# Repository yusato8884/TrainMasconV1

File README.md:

# TrainMasconV1

自作ゲーム「[Tozai Sim Pro](https://tozai-sim.base44.app/)」用の、USBキーボードとして動作する自作マスコン（主幹制御器）コントローラーです。
可変抵抗（2連ボリューム）のレバー位置を読み取り、ノッチ（P4〜N〜B7〜EB）に応じたキー入力をPCへ送ります。
現在のノッチは0.96インチOLEDに大きく表示されます。

- マイコン: AE-RP2040（MicroPython）
- 表示: SSD1306 OLED 128x64（I2C）
- 入力: 可変抵抗 1個（ADC）＋ ボタン 3個
- 接続: USB HID キーボード

ドキュメント: <https://y-trm1doc.base44.app/>

## ディレクトリ構成

```
Firmware/
  LICENSE                               ソフトウェアのライセンス（MIT）
  main.py                               本体ファームウェア（ノッチ→キー入力、OLED表示、USB HID）
  vrcalib.py                            可変抵抗の電圧測定ツール（ノッチ境界の電圧調整用）
Hardware/
  Enclosure/                            3Dプリント用ケース
    TRM1-Case-Top.stl                   ケース上部
    TRM1-Case-Bottom.stl                ケース下部
    TRM1-Case-Handle.stl                ハンドル
    TRM1-Case-Handle-Stopper.stl        ハンドルのストッパー
  PCB/                                  基板データ
    ProPrj_Mascon_2026-09-23.epro2      EasyEDA Pro の原本
    kicad_output/                       KiCad 8 変換版
      Mascon.kicad_pro                  KiCad プロジェクトファイル
      Mascon.kicad_sch                  回路図
      Mascon.kicad_pcb                  基板
      Mascon.kicad_sym                  シンボルライブラリ
      Mascon.kicad_footprints.pretty/   フットプリントライブラリ（.kicad_mod 8点）
      fp-lib-table                      フットプリントライブラリ設定
      sym-lib-table                     シンボルライブラリ設定
      CONVERSION_NOTES.md               変換時の注意事項
  LICENSE                               ハードウェアのライセンス（CERN-OHL-P v2）
README.md                               このファイル
```

## 配線

| 部品 | ピン |
|---|---|
| OLED SDA / SCL | GP20 / GP19（SoftI2C, アドレス 0x3C） |
| ボタン1 / 2 / 3 | GP23 / GP24 / GP25（GND側に接続） |
| 可変抵抗（中点） | GP26 (ADC0)、両端は 3V3 と GND |

## セットアップ

1. AE-RP2040 に MicroPython を書き込みます。
2. 必要なライブラリを導入します。
   ```
   mpremote mip install ssd1306
   mpremote mip install usb-device-keyboard
   ```
3. `Firmware/main.py` を `main.py` として本体に転送します。
4. USBで接続すると、キーボードとして認識されます。

## ノッチの調整

1. `Firmware/vrcalib.py` を実行し、レバーを各ノッチに合わせたときの電圧を読み取ります。
2. `main.py` の `LAYERS` の電圧しきい値（下限V, 上限V）を書き換えます。

既定のキー割り当ては次のとおりです（電圧の低い側から）。

| ノッチ | P4 | P3 | P2 | P1 | N | B1〜B6 | B7 | EB |
|---|---|---|---|---|---|---|---|---|
| キー | 1 | 2 | 3 | 4 | → | 5, 6, 7, 8, 9, 0 | - | Space |

ボタン1を押しながら起動すると安全モード（HID初期化とメインループを行わない）になり、ファイルを編集できます。

## ハードウェア

- `Hardware/PCB/ProPrj_Mascon_2026-09-23.epro2` が基板の原本です。
- `Hardware/PCB/kicad_output/` は KiCad 8 向けの変換結果です（開く場合は `Mascon.kicad_pro` を指定します）。KiCad での動作確認は未実施のため、開く際は [CONVERSION_NOTES.md](Hardware/PCB/kicad_output/CONVERSION_NOTES.md) を確認してください。
- ケースのSTL（`Hardware/Enclosure/` 内の `TRM1-Case-*.stl` 4点）についての注意:
  - サポート材は含まれていません。造形方向やプリンターに応じて、必要ならスライサー側で追加してください。
  - 薄肉部分やクリアランス（はめ合いの隙間）は十分に考慮されていません。
  - そのため、3Dプリントサービスに発注するか、自分で造形する場合は精度の非常に高いプリンター（光造形など）が必要です。一般的なFDMプリンターでは、そのままでは組み立てられない可能性があります。

## ライセンス

ライセンスは、対象ごとにそれぞれのフォルダ内の `LICENSE` に記載されています。

| 対象 | ライセンス | ファイル |
|---|---|---|
| ハードウェア（`Hardware/` 配下: 基板、回路図、ケース） | [CERN-OHL-P v2](Hardware/LICENSE) | `Hardware/LICENSE` |
| ソフトウェア（`Firmware/` 配下） | [MIT](Firmware/LICENSE) | `Firmware/LICENSE` |

SPDX: `CERN-OHL-P-2.0`（ハードウェア）/ `MIT`（ソフトウェア）

[SCANOSS](https://www.scanoss.com/) によるスキャンでは、全ファイルで既存OSSとの一致は検出されませんでした（2026-09-24時点）。

---

# TrainMasconV1

A custom mascon (master controller) controller for my original game "[Tozai Sim Pro](https://tozai-sim.base44.app/)", which operates as a USB keyboard.
It reads the lever position of a variable resistor (dual-gang potentiometer) and sends key inputs to the PC according to the notch (P4〜N〜B7〜EB).
The current notch is displayed prominently on a 0.96-inch OLED.

- Microcontroller: AE-RP2040 (MicroPython)
- Display: SSD1306 OLED 128x64 (I2C)
- Input: 1 variable resistor (ADC) + 3 buttons
- Connection: USB HID keyboard

Documentation: <https://y-trm1doc.base44.app/>

## Directory Structure

```
Firmware/
  LICENSE                               Software license (MIT)
  main.py                               Main firmware (notch→key input, OLED display, USB HID)
  vrcalib.py                            Variable resistor voltage measurement tool (for adjusting notch boundary voltages)
Hardware/
  Enclosure/                            3D-printable case
    TRM1-Case-Top.stl                   Case top
    TRM1-Case-Bottom.stl                Case bottom
    TRM1-Case-Handle.stl                Handle
    TRM1-Case-Handle-Stopper.stl        Handle stopper
  PCB/                                  PCB data
    ProPrj_Mascon_2026-09-23.epro2      EasyEDA Pro original
    kicad_output/                       KiCad 8 converted version
      Mascon.kicad_pro                  KiCad project file
      Mascon.kicad_sch                  Schematic
      Mascon.kicad_pcb                  PCB layout
      Mascon.kicad_sym                  Symbol library
      Mascon.kicad_footprints.pretty/   Footprint library (8 .kicad_mod files)
      fp-lib-table                      Footprint library table
      sym-lib-table                     Symbol library table
      CONVERSION_NOTES.md               Notes on the conversion
  LICENSE                               Hardware license (CERN-OHL-P v2)
README.md                               This file
```

## Wiring

| Component | Pin |
|---|---|
| OLED SDA / SCL | GP20 / GP19（SoftI2C, address 0x3C） |
| Button 1 / 2 / 3 | GP23 / GP24 / GP25（connected to GND） |
| Variable resistor (center tap) | GP26 (ADC0), both ends to 3V3 and GND |

## Setup

1. Flash MicroPython onto the AE-RP2040.
2. Install the required libraries.
   ```
   mpremote mip install ssd1306
   mpremote mip install usb-device-keyboard
   ```
3. Transfer `Firmware/main.py` to the device as `main.py`.
4. When connected via USB, it will be recognized as a keyboard.

## Notch Adjustment

1. Run `Firmware/vrcalib.py` and measure the voltage when the lever is set to each notch.
2. Rewrite the voltage thresholds (lower limit V, upper limit V) in `LAYERS` in `main.py`.

The default key assignments are as follows (from the lower-voltage side).

| Notch | P4 | P3 | P2 | P1 | N | B1〜B6 | B7 | EB |
|---|---|---|---|---|---|---|---|---|
| Key | 1 | 2 | 3 | 4 | → | 5, 6, 7, 8, 9, 0 | - | Space |

Starting while holding Button 1 enters safe mode (HID initialization and the main loop are not executed), allowing files to be edited.

## Hardware

- `Hardware/PCB/ProPrj_Mascon_2026-09-23.epro2` is the original PCB design file.
- `Hardware/PCB/kicad_output/` contains the conversion results for KiCad 8 (open `Mascon.kicad_pro` to load the project). Since operation in KiCad has not been verified, check [CONVERSION_NOTES.md](Hardware/PCB/kicad_output/CONVERSION_NOTES.md) when opening the files.
- Notes on the case STL files (the four `TRM1-Case-*.stl` files in `Hardware/Enclosure/`):
  - Support material is not included. Add it in the slicer as necessary depending on the print orientation and printer.
  - Thin sections and clearances (gaps for fitting) have not been sufficiently taken into consideration.
  - Therefore, if ordering from a 3D printing service, or printing it yourself, a very high-precision printer (such as a resin printer) is required. With a typical FDM printer, it may not be possible to assemble it as-is.

## License

The license for each part is provided in the `LICENSE` file inside the corresponding folder.

| Target | License | File |
|---|---|---|
| Hardware (PCB, schematics, and case under `Hardware/`) | [CERN-OHL-P v2](Hardware/LICENSE) | `Hardware/LICENSE` |
| Software (under `Firmware/`) | [MIT](Firmware/LICENSE) | `Firmware/LICENSE` |

SPDX: `CERN-OHL-P-2.0` (hardware) / `MIT` (software)

According to a scan by [SCANOSS](https://www.scanoss.com/), no matches with existing OSS were detected across all files (as of 2026-09-24).

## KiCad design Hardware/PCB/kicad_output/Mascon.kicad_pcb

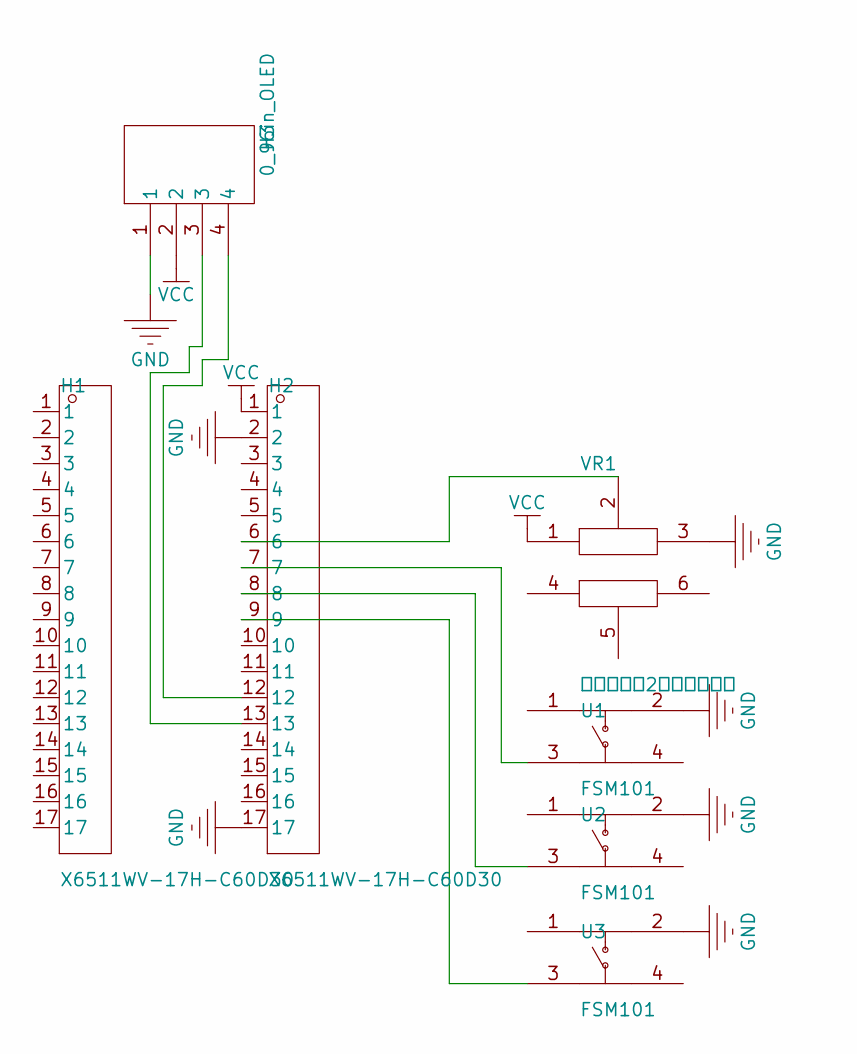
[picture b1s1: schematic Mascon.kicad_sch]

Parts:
H1, H2: X6511WV-17H-C60D30; HDR-TH_17P-P2.54-V-M; MPN X6511WV-17H-C60D30; LCSC C725949
H3: 0_96in_OLED
U1, U2, U3: FSM101; SW-TH_4P-L12.0-W12.0-P5.00-LS12.5; MPN FSM101; LCSC C5340381
VR1: 基板取付用2連ボリューム

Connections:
$1N9: H2.6, VR1.2
$1N14: H2.7, U1.3
$1N15: H2.8, U2.3
$1N16: H2.9, U3.3
$1N21: H2.12, H3.4
$1N22: H2.13, H3.3
GND: H2.2, H2.17, H3.1, U1.2, U2.2, U3.2, VR1.3
VCC: H2.1, H3.2, VR1.1

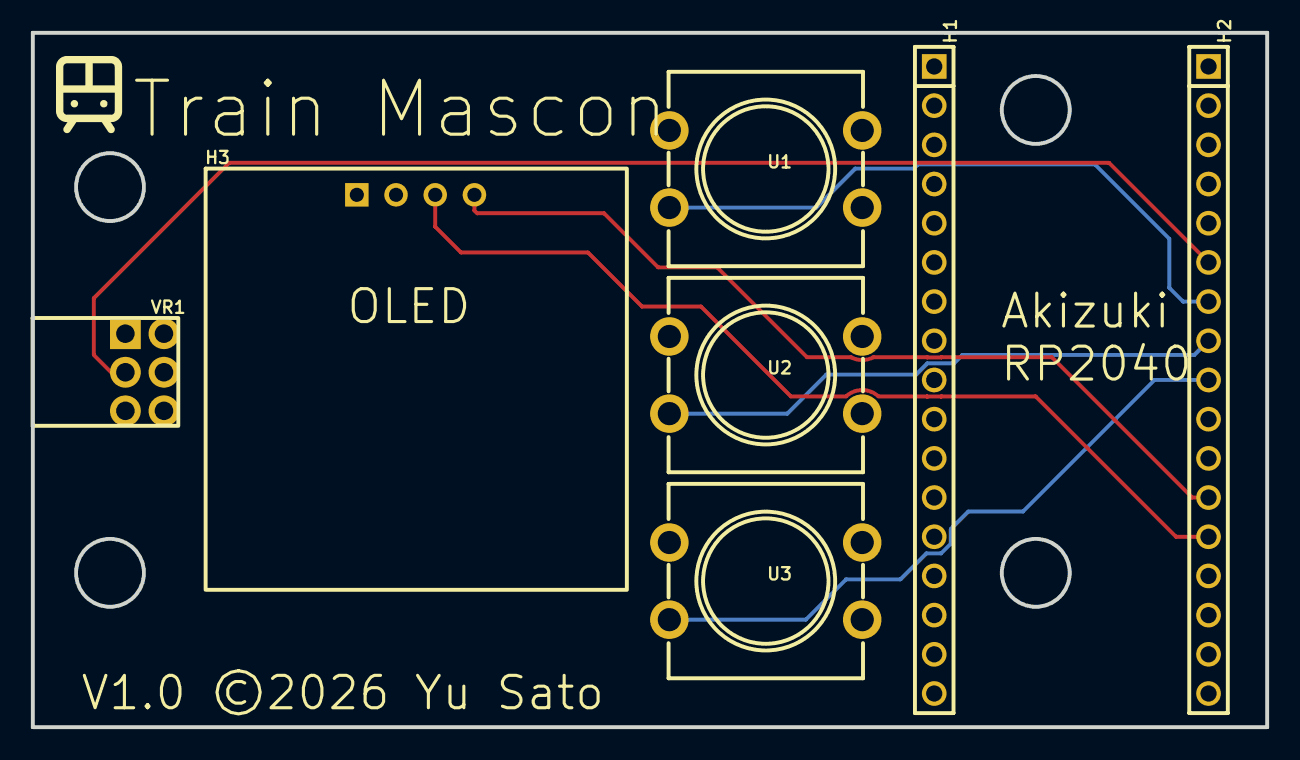
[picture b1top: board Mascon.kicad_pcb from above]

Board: 4 copper layers, 80.0 x 45.0 mm, 7 parts (0 on the bottom side), 8 nets.

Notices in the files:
Hardware/PCB/kicad_output/Mascon.kicad_pcb:
V1.0 ©2026 Yu Sato
